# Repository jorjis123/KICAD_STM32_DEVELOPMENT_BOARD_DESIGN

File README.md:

Core MCU: STM32 with access to essential debug/programming interfaces (SWD/SWO/NRST, UART, I2C).

🔹 Power: USB input and dedicated 12V jack, with on-board buck converter for stable 3.3V supply.

🔹 Connectivity: Breakout headers for easy prototyping.

🔹 Layout focus: Optimized ground plane distribution, decoupling capacitors placed for noise reduction, and routing for signal integrity.

🔹 Applications: Ideal for embedded firmware development, educational use, and rapid prototyping.

This project gave me great hands-on experience in schematic capture, PCB layout, power distribution, and embedded hardware design best practices.

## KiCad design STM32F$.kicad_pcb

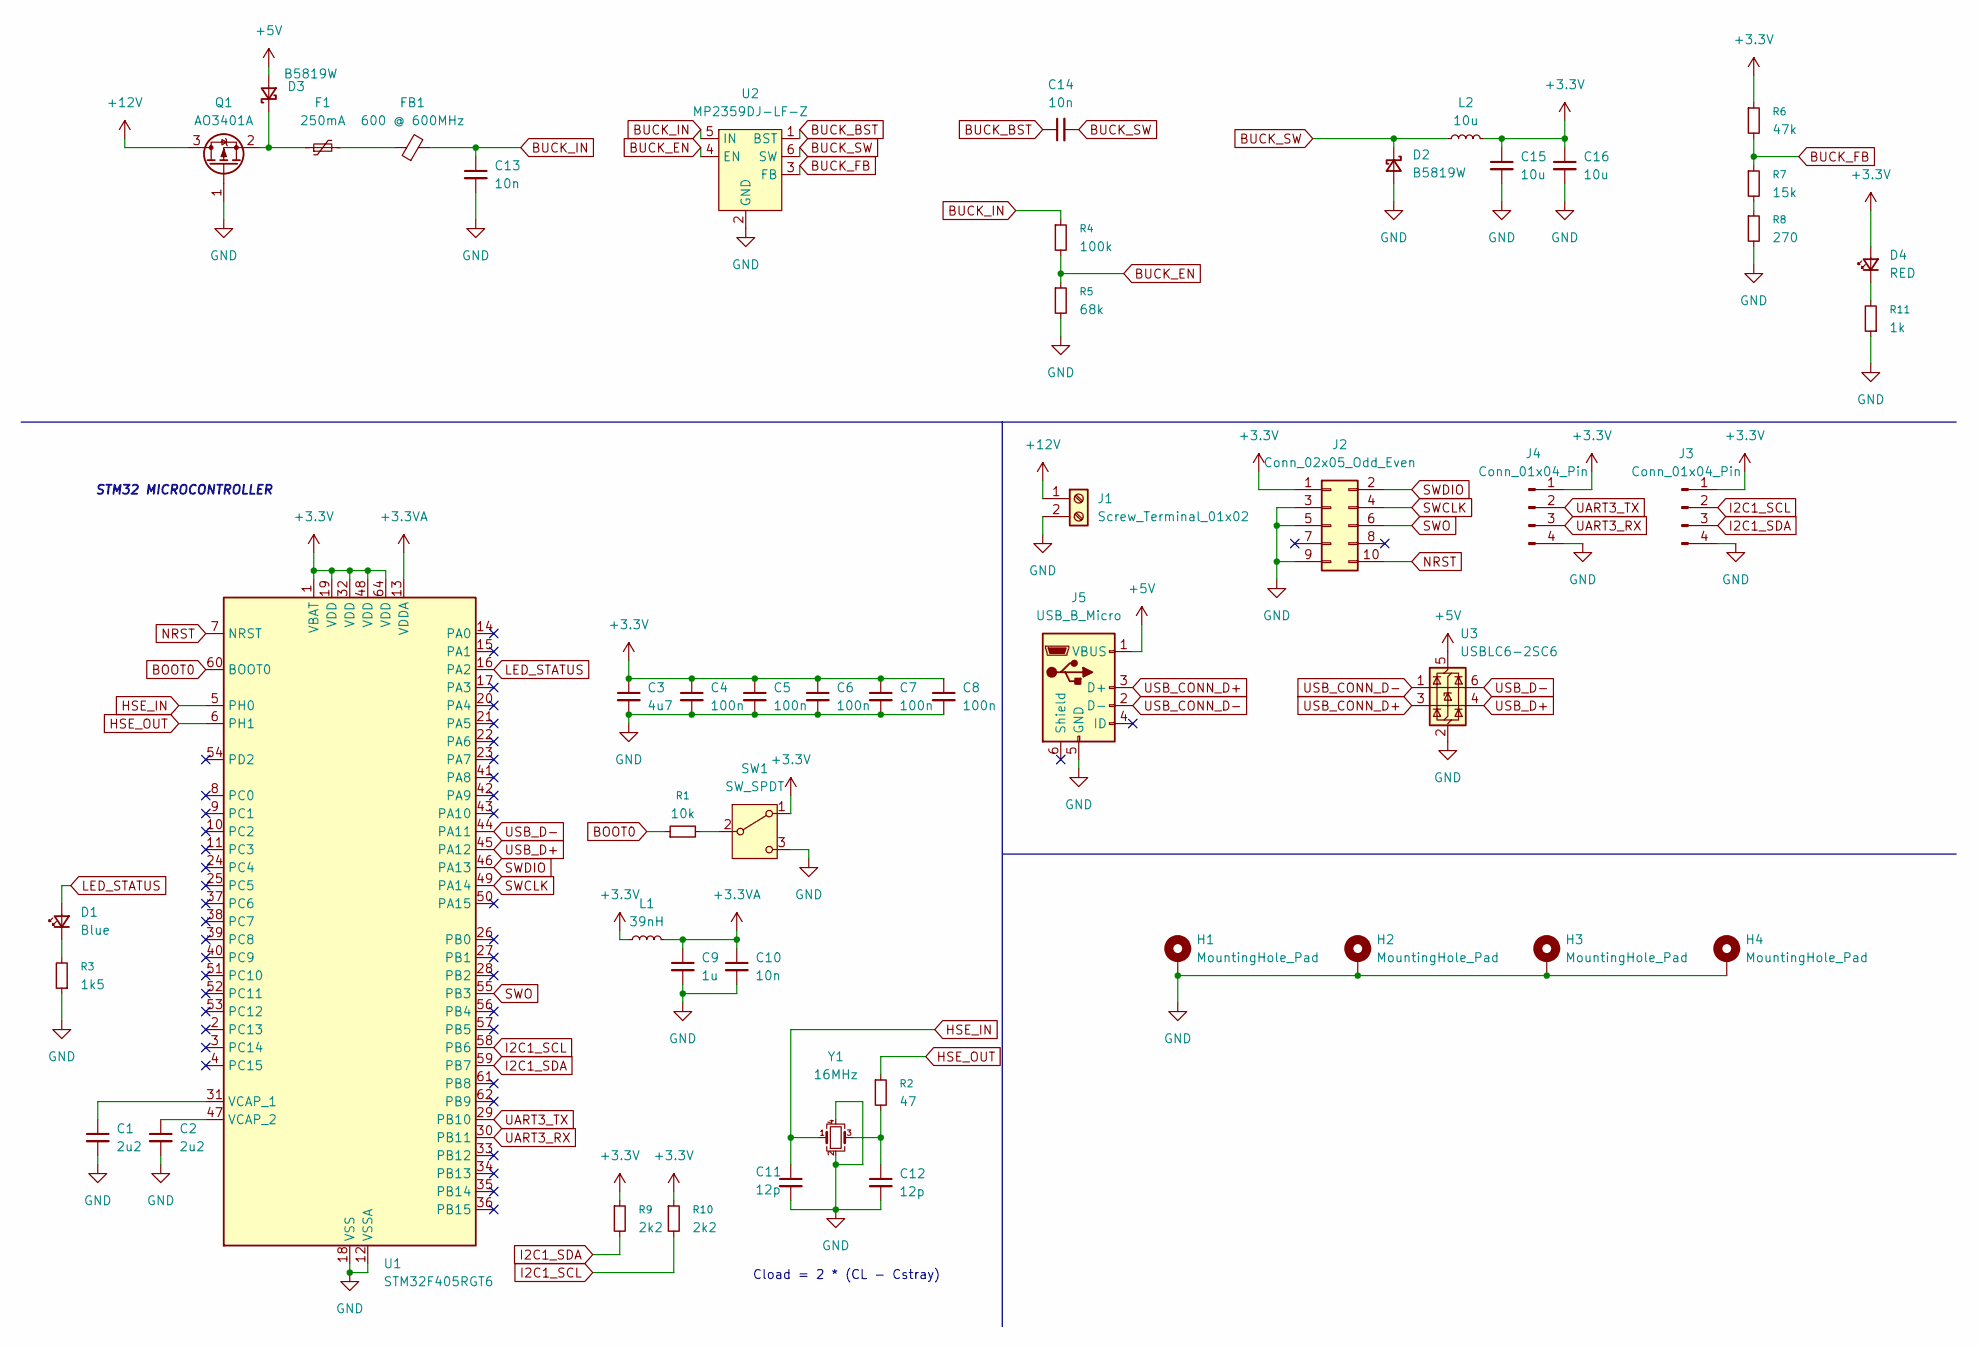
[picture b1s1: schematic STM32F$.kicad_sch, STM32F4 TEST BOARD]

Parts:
C1, C2: 2u2; C_0603_1608Metric
C3: 4u7; C_0603_1608Metric
C4, C5, C6, C7, C8: 100n; C_0402_1005Metric
C9: 1u; C_0402_1005Metric
C10: 10n; C_0402_1005Metric
C11, C12: 12p; C_0402_1005Metric
C13, C14: 10n; C_0603_1608Metric
C15, C16: 10u; C_1206_3216Metric
D1: Blue; LED_0603_1608Metric
D2, D3: B5819W; D_SOD-123
D4: RED; LED_0603_1608Metric
F1: 250mA; Fuse_1206_3216Metric
FB1: 600 @ 600MHz; L_0805_2012Metric
H1, H2, H3, H4: MountingHole_Pad; MountingHole_4.3mm_M4_Pad_Via
J1: Screw_Terminal_01x02; TerminalBlock_Phoenix_PT-1,5-2-3.5-H_1x02_P3.50mm_Horizontal
J2: Conn_02x05_Odd_Even; PinSocket_2x05_P1.27mm_Vertical_SMD
J3, J4: Conn_01x04_Pin; PinHeader_1x04_P1.00mm_Vertical
J5: USB_B_Micro; USB_Micro-B_Molex_47346-0001
L1: 39nH; L_0402_1005Metric
L2: 10u; L_Sunlord_SWPA8040S
Q1: AO3401A; SOT-23
R1: 10k; R_0603_1608Metric
R2: 47; R_0402_1005Metric
R3: 1k5; R_0603_1608Metric
R4: 100k; R_0402_1005Metric
R5: 68k; R_0402_1005Metric
R6: 47k; R_0402_1005Metric
R7: 15k; R_0603_1608Metric
R8: 270; R_0402_1005Metric
R9, R10: 2k2; R_0402_1005Metric
R11: 1k; R_0402_1005Metric
SW1: SW_SPDT; SW_SPDT_PCM12
U1: STM32F405RGT6; LQFP-64_10x10mm_P0.5mm
U2: MP2359DJ-LF-Z; SOT-23-6
U3: USBLC6-2SC6; SOT-23-6
Y1: 16MHz; Crystal_SMD_3225-4Pin_3.2x2.5mm

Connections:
+3.3V: C3.1, C4.1, C5.1, C6.1, C7.1, C8.1, C15.1, C16.1, D4.2 (A), J2.1, J3.1, J4.1, L1.1, L2.2, R6.1, R9.1, R10.1, SW1.1 (A), U1.1 (VBAT), U1.19 (VDD), U1.32 (VDD), U1.48 (VDD), U1.64 (VDD)
+3.3VA: C9.1, C10.1, L1.2, U1.13 (VDDA)
+5V: D3.2 (A), J5.1 (VBUS), U3.5 (VBUS)
+12V: J1.1, Q1.3 (D)
BOOT0: R1.1, U1.60 (BOOT0)
BUCK_BST: C14.1, U2.1 (BST)
BUCK_EN: R4.2, R5.1, U2.4 (EN)
BUCK_FB: R6.2, R7.1, U2.3 (FB)
BUCK_IN: C13.1, FB1.2, R4.1, U2.5 (IN)
BUCK_SW: C14.2, D2.1 (K), L2.1, U2.6 (SW)
GND: C1.2, C2.2, C3.2, C4.2, C5.2, C6.2, C7.2, C8.2, C9.2, C10.2, C11.2, C12.2, C13.2, C15.2, C16.2, D2.2 (A), H1.1, H2.1, H3.1, H4.1, J1.2, J2.3, J2.5, J2.9, J3.4, J4.4, J5.5 (GND), Q1.1 (G), R3.1, R5.2, R8.2, R11.1, SW1.3 (C), U1.12 (VSSA), U1.18 (VSS), U1.63 (VSS), U2.2 (GND), U3.2 (GND), Y1.2, Y1.4
HSE_IN: C11.1, U1.5 (PH0), Y1.1
HSE_OUT: R2.1, U1.6 (PH1)
I2C1_SCL: J3.2, R10.2, U1.58 (PB6)
I2C1_SDA: J3.3, R9.2, U1.59 (PB7)
LED_STATUS: D1.2 (A), U1.16 (PA2)
NRST: J2.10, U1.7 (NRST)
unnamed: C12.1, R2.2, Y1.3
unnamed: D1.1 (K), R3.2
unnamed: D3.1 (K), F1.1, Q1.2 (S)
unnamed: D4.1 (K), R11.2
unnamed: F1.2, FB1.1
unnamed: R7.2, R8.1
unnamed: R1.2, SW1.2 (B)
unnamed: C1.1, U1.31 (VCAP_1)
unnamed: C2.1, U1.47 (VCAP_2)
SWCLK: J2.4, U1.49 (PA14)
SWDIO: J2.2, U1.46 (PA13)
SWO: J2.6, U1.55 (PB3)
UART3_RX: J4.3, U1.30 (PB11)
UART3_TX: J4.2, U1.29 (PB10)
USB_CONN_D+: J5.3 (D+), U3.3 (I/O2)
USB_CONN_D-: J5.2 (D-), U3.1 (I/O1)
USB_D+: U1.45 (PA12), U3.4 (I/O2)
USB_D-: U1.44 (PA11), U3.6 (I/O1)

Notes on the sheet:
STM32 MICROCONTROLLER
Cload = 2 * (CL - Cstray)

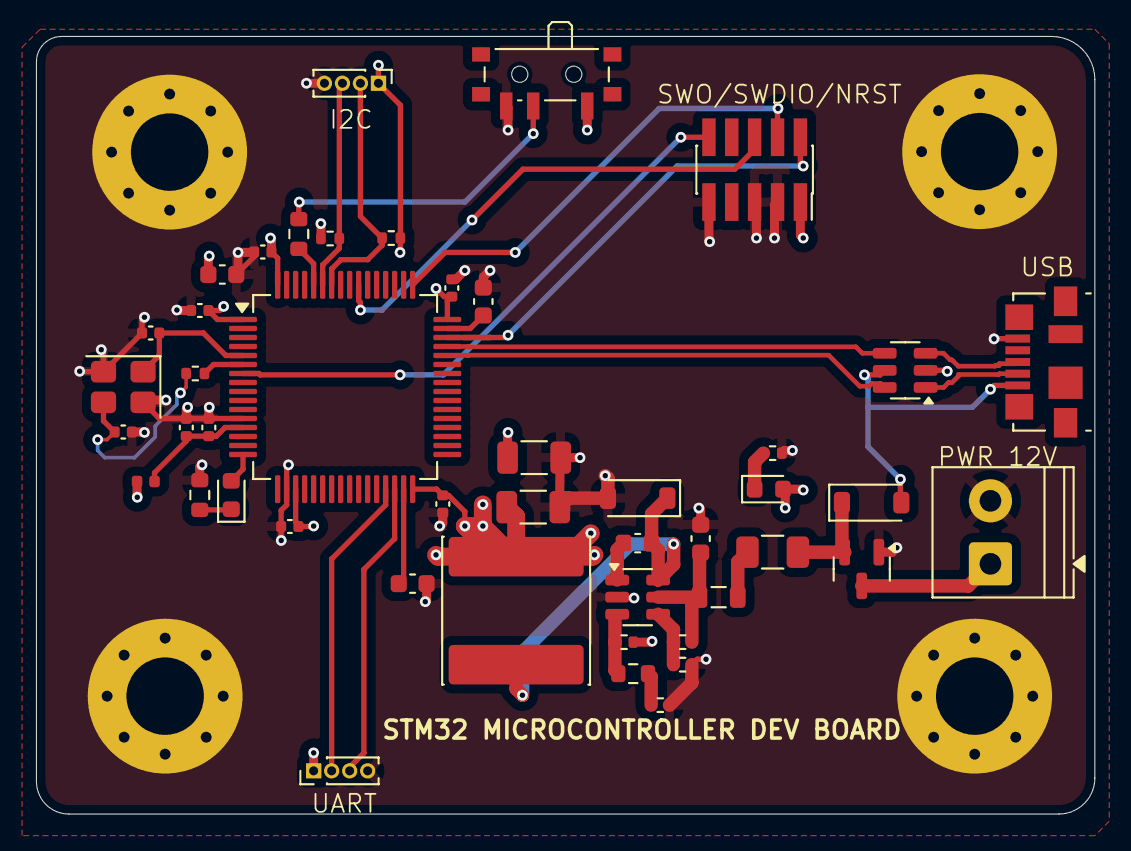
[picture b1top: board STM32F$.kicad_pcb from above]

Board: 4 copper layers, 58.8 x 43.2 mm, 50 parts (0 on the bottom side), 35 nets.
